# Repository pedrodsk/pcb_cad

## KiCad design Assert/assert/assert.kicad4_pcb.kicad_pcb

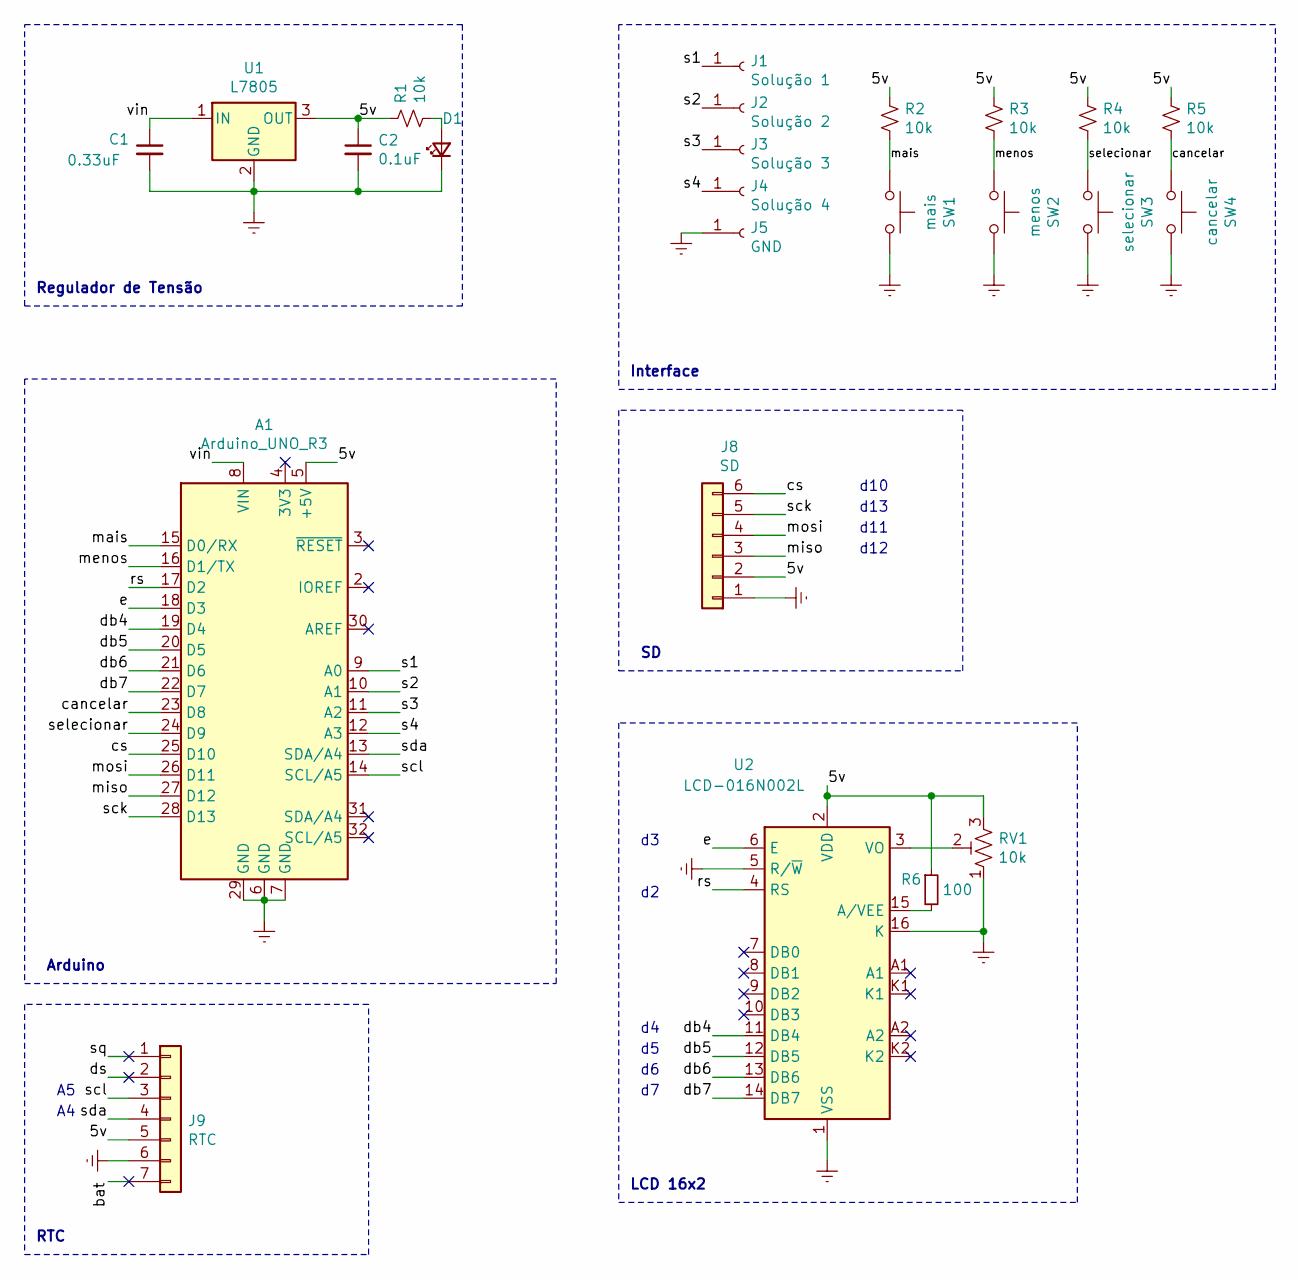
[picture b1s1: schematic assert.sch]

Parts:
A1: Arduino_UNO_R3
C1: 0.33uF; C_Disc_D3.0mm_W1.6mm_P2.50mm
C2: 0.1uF; C_Disc_D3.0mm_W1.6mm_P2.50mm
D1: LED_Small; LED_D3.0mm
J1: Solução 1; Banana_Jack_1Pin
J2: Solução 2; Banana_Jack_1Pin
J3: Solução 3; Banana_Jack_1Pin
J4: Solução 4; Banana_Jack_1Pin
J5: GND; Banana_Jack_1Pin
J8: SD; PinSocket_1x06_P2.54mm_Vertical
J9: RTC; PinSocket_1x07_P2.54mm_Vertical
R1, R2, R3, R4, R5: 10k; R_Axial_DIN0207_L6.3mm_D2.5mm_P7.62mm_Horizontal
R6: 100; R_Axial_DIN0207_L6.3mm_D2.5mm_P7.62mm_Horizontal
RV1: 10k; Potentiometer_Bourns_3386C_Horizontal
SW1: mais; SW_PUSH_6mm
SW2: menos; SW_PUSH_6mm
SW3: selecionar; SW_PUSH_6mm
SW4: cancelar; SW_PUSH_6mm
U1: L7805; TO-220-3_Horizontal_TabDown
U2: LCD-016N002L; WC1602A

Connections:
/5v: A1.5 (+5V), C2.1, J8.2, J9.5, R1.1, R2.1, R3.1, R4.1, R5.1, R6.1, RV1.3, U1.3 (OUT), U2.2 (VDD)
/bat: J9.7
/cancelar: A1.23 (D8), R5.2, SW4.1
/cs: A1.25 (D10), J8.6
/db4: A1.19 (D4), U2.11 (DB4)
/db5: A1.20 (D5), U2.12 (DB5)
/db6: A1.21 (D6), U2.13 (DB6)
/db7: A1.22 (D7), U2.14 (DB7)
/ds: J9.2
/e: A1.18 (D3), U2.6 (E)
/mais: A1.15 (D0/RX), R2.2, SW1.1
/menos: A1.16 (D1/TX), R3.2, SW2.1
/miso: A1.27 (D12), J8.3
/mosi: A1.26 (D11), J8.4
/rs: A1.17 (D2), U2.4 (RS)
/s1: A1.9 (A0), J1.1
/s2: A1.10 (A1), J2.1
/s3: A1.11 (A2), J3.1
/s4: A1.12 (A3), J4.1
/sck: A1.28 (D13), J8.5
/scl: A1.14 (SCL/A5), J9.3
/sda: A1.13 (SDA/A4), J9.4
/selecionar: A1.24 (D9), R4.2, SW3.1
/sq: J9.1
/vin: A1.8 (VIN), C1.1, U1.1 (IN)
unnamed: D1.2 (A), R1.2
unnamed: R6.2, U2.15 (A/VEE)
unnamed: RV1.2, U2.3 (VO)

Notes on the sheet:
Regulador de Tensão
LCD 16x2
d12
d11
d13
d10
Interface
RTC
Arduino

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
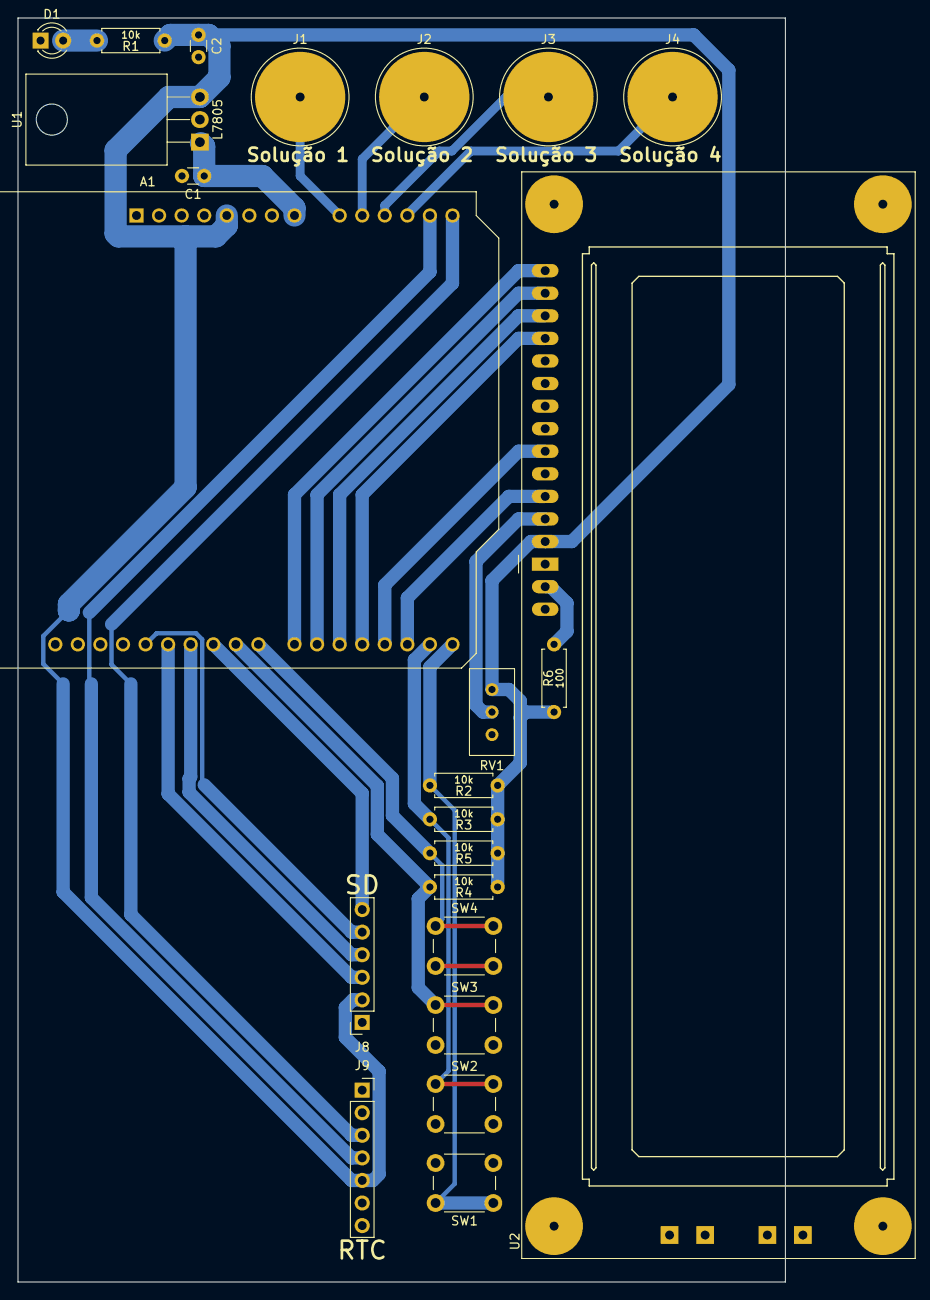
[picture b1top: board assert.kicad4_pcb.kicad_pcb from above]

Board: 2 copper layers, 86.4 x 142.2 mm, 23 parts (0 on the bottom side), 26 nets.

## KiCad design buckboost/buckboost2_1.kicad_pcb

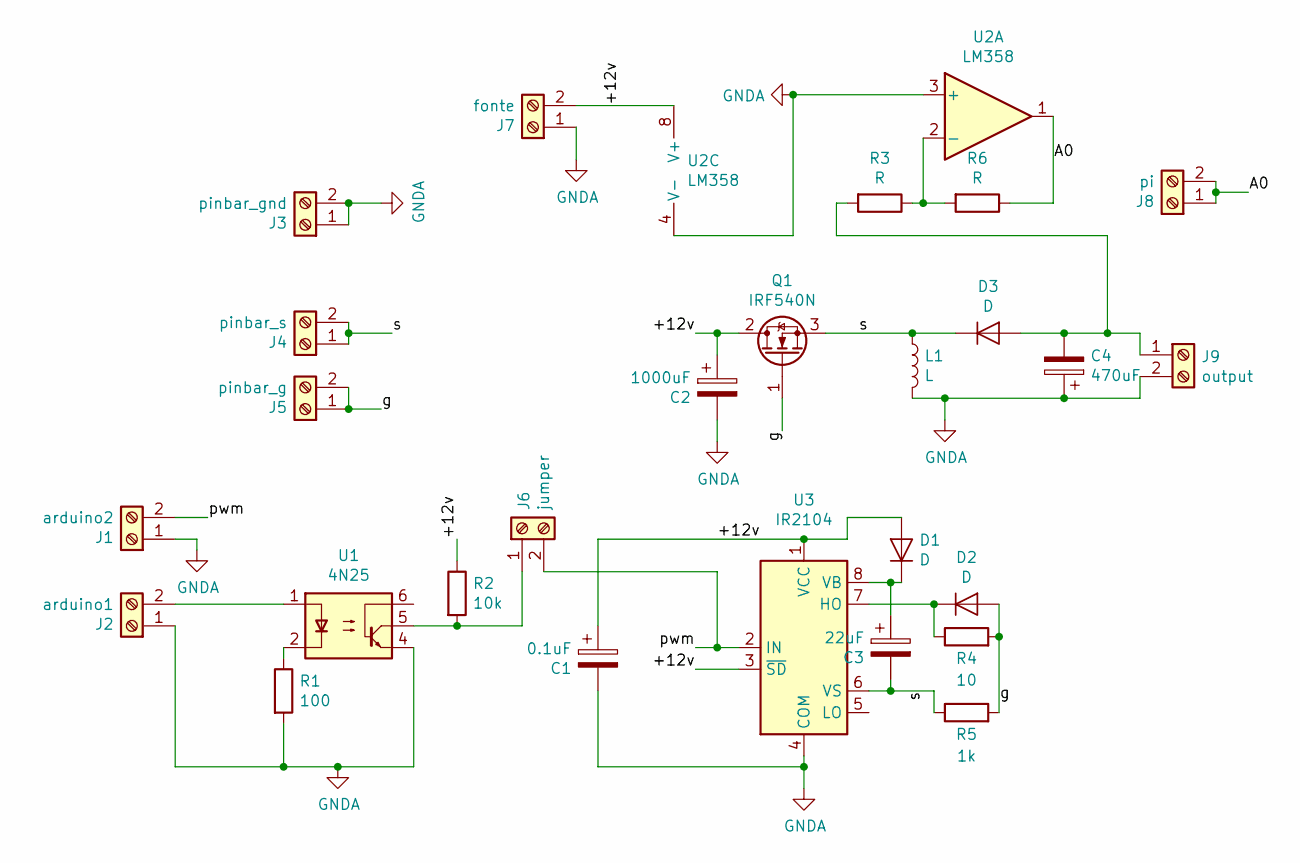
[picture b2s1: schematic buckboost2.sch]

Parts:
C1: 0.1uF; CP_Radial_D5.0mm_P2.50mm
C2: 1000uF; CP_Radial_D5.0mm_P2.50mm
C3: 22uF; CP_Radial_D5.0mm_P2.50mm
C4: 470uF; CP_Radial_D12.5mm_P5.00mm
D1, D2: D; D_A-405_P7.62mm_Horizontal
D3: D; D_P600_R-6_P20.00mm_Horizontal
J1: arduino2; TerminalBlock_bornier-2_P5.08mm
J2: arduino1; TerminalBlock_bornier-2_P5.08mm
J3: pinbar_gnd; TerminalBlock_bornier-2_P5.08mm
J4: pinbar_s; TerminalBlock_bornier-2_P5.08mm
J5: pinbar_g; TerminalBlock_bornier-2_P5.08mm
J6: jumper; TerminalBlock_bornier-2_P5.08mm
J7: fonte; TerminalBlock_bornier-2_P5.08mm
J8: pi; TerminalBlock_bornier-2_P5.08mm
J9: output; TerminalBlock_bornier-2_P5.08mm
L1: L; L_Toroid_Horizontal_D12.7mm_P20.00mm_Diameter14-5mm_Amidon-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
Q1: IRF540N; TO-220-3_Vertical
R1: 100; R_Axial_DIN0204_L3.6mm_D1.6mm_P7.62mm_Horizontal
R2: 10k; R_Axial_DIN0204_L3.6mm_D1.6mm_P5.08mm_Horizontal
R3, R6: R; R_Axial_DIN0204_L3.6mm_D1.6mm_P5.08mm_Horizontal
R4: 10; R_Axial_DIN0204_L3.6mm_D1.6mm_P5.08mm_Horizontal
R5: 1k; R_Axial_DIN0204_L3.6mm_D1.6mm_P5.08mm_Horizontal
U1: 4N25; DIP-6_W7.62mm
U2: LM358; DIP-8_W7.62mm_LongPads
U3: IR2104; DIP-8_W7.62mm_LongPads

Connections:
/+12v: C1.1, C2.1, D1.2 (A), J7.2, Q1.2 (D), R2.1, U2.8 (V+), U3.1 (VCC), U3.3 (~SD)
/A0: J8.1, J8.2, R6.1, U2.1
/g: D2.2 (A), J5.1, J5.2, Q1.1 (G), R4.2, R5.2
/pwm: J1.2, J6.2, U3.2 (IN)
/s: C3.2, D3.1 (K), J4.1, J4.2, L1.1, Q1.3 (S), R5.1, U3.6 (VS)
GNDA: C1.2, C2.2, C4.1, J1.1, J2.1, J3.1, J3.2, J7.1, J9.2, L1.2, R1.2, U1.4, U2.3 (+), U2.4 (V-), U3.4 (COM)
unnamed: C3.1, D1.1 (K), U3.8 (VB)
unnamed: C4.2, D3.2 (A), J9.1, R3.2
unnamed: D2.1 (K), R4.1, U3.7 (HO)
unnamed: J2.2, U1.1
unnamed: J6.1, R2.2, U1.5
unnamed: R1.1, U1.2
unnamed: R3.1, R6.2, U2.2 (-)

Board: 2 copper layers, 27 parts (0 on the bottom side), 13 nets, no tracks yet.
